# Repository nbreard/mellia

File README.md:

# MD10 board

Environnement setup : 

Software :

 STM32CubeIDE : for compilation debugging and flashing 
		
 STM32CubeProgrammer: for deactivate write protection bit

Hardware : LoRaWAN gateway connected to LoRaWAN server (TTN)

# MELLIA - Kit Dadant 10

## Présentation

Le kit Mellia Dadant 10 est un ensemble de capteurs connectés permettant d’obtenir des informations essentielles relatives à l’exploitation d’une ruche dans l’objectif de suivre l’évolution de la colonie en réduisant le nombre d’interventions intrusives et les déplacement de l’apiculteur.

Ce kit s’adapte sur une ruche Dadant 10, le modèle le plus utilisé actuellement. Il comprend un dispositif de pesée électronique, un dispositif de mesure de température et humidité intérieure et extérieure, un capteur de pression atmosphérique ainsi qu’un module de communication sans fil. L’ensemble des acquisitions sont enregistrées dans une base de données, un tableau de bord permet le suivi de l’état de la ruche.

## Fonctionnalités

### Mesure poids de la ruche

On pèse la ruche à intervalle régulier pour faire remonter une donnée sur la masse à l’apiculteur. Cela permet d’obtenir un indice de l’état de santé de la colonie et d’envisager d’intervenir ou non sur la ruche (rajout de candi, miellée etc). 

### Température extérieure

Une captation de température dans l’environnement immédiat de la ruche renseigne l’apiculteur sur la météo du milieu dans lequel évolue la colonie d’abeille et donne la capacité d’anticiper une miellée par exemple.

### Température intérieure

La mesure de la température à l’intérieur de la ruche fournis une information sur l’état de santé du couvain. Pour se développer correctement sa température doit rester dans une plage de mesure de 18 à 35°C. Sortir de cette plage indique un danger pour la colonie. Des variations régulières de la température est un signe d’essaimage.

### Humidité extérieure

Utile au rafraîchissement de la ruche ou intervenant directement dans la probabilité de voir se développer des champignons, le taux d’humidité intervient directement dans la vie de la colonie et le mesurer peut se révéler être un élément clé pour comprendre l’activité de la ruche.

### Humidité intérieure

Cette donnée a une incidence sur l’état de santé du couvain, en effet si celui ci est trop humide les parois en deviennent fragiles. Le taux d’humidité est aussi un bon indicateur de la qualité du miel.

### Pression atmosphérique

En corrélation avec l’humidité et la température extérieure, la pression atmosphérique fournit à l’apiculteur une vision globale sur le milieu à proximité de la ruche et sur les éléments auxquels sont soumis les abeilles 

### [Tableau de bord](https://grafana.mellia.lab.open.studio/login "https://grafana.mellia.lab.open.studio/login")

Pour faciliter l’information et la prise de décision les données sont rassemblées dans un tableau de bords consultable en ligne.

## Notice

### Composants du kit

Pour les composants sur la carte se référer au document md10-board/hardware/wheather_board_v1/wheather_board_v1.csv

| composant                            | référence                |
| ------                               | ------                   |
| jauge de contrainte                  | tedea 1242               |
| antenne                              | MOLEX  105262-0001       |
| boîtier                              | TAM 131007 ENCLOSURE     |
| panneau solaire + batterie           |                          |

### Montage

### Mise en œuvre

## Software 

**Prérequis** : 

Télécharger le logiciel STM32CubeIDE : <https://www.st.com/en/development-tools/stm32cubeide.html>

Télécharger le logiciel STM32CubeProgrammer : <https://www.st.com/en/development-tools/stm32cubeide.html>

Télécharger le code grâce à la commande suivante : 

Git clone <https://gitlab.openstudio-lab.com/mellia/mellia.git>

**Ouvrir le projet :** 

Ouvrir stm32CubeIde, sélectionner ~/md10-board/software/ruche\_soft comme workspace

Depuis STM32CubeIDE, cliquer sur File et « Open Project from file system »

Dans la fenêtre qui s’ouvre cliquer sur directory et sélectionner : ~/md10-board/software/ruche\_soft/STM32Cube\_FW\_WL\_V1.1.0/Projects/NUCLEO-WL55JC/Applications/LoRaWAN/LoRaWAN\_End\_Node/STM32CubeIDE

Les librairies des composants sont accessibles depuis Drivers. Le dossier Sensors contient les fonctions des différentes de mesures, poids, température etc.

Application contient le code de la machine à état qui fait tourner le programme mais aussi les drivers des périphériques de communication tel que le SPi l’i2c ou encore le protocole de communication LoRaWAN servant à faire remonter les données.

L’acquisition des mesures est faite au cours de la fonction SendTxData située dans lora\_app.c

**Flasher le programme :**

Connecter le debugger : 

Se connecter au microcontrolleur en utilise STM32Cubeprogramme et désactiver la protection en écriture : 

Pour lancer le debugger depuis stmcubeide appliquer cette configuration depuis Run -> debug configuration : 

Attention pour des raisons d’optimisation la sonde de debug et le mode low power est activé. Pour faire plus que flasher le code est debugger en mode pas à pas il faut se rendre dans sys\_conf.h et régler sur 1 les #define suivants : DEBUGGER\_ENABLED et LOW\_POWER\_DISABLE

**Procédure de calibration de la balance** 

On utilise les équations données par TI dans le document relatif à la bonne utilisation de la carte ADS1242 : 

On a besoin de 3 paramètres : 

- wfs  : la masse la plus proche possible de la pleine échelle
- Cfs  : la sortie de l’dc correspondant à wfs
- Czs : la sortie de l’adc lorsque la balance est à vide

À l’aide de ces trois données on peut en déduire l’équation 1 puis la 2 . On place un points d’arrêt dans le code après la mesure pour récupérer cfs et czs.

Les paramètres wzs et m sont à introduire en dur dans le code dans la fonction d’initialisation de l’ads1232 : void ADS1232Sensors\_Init(sensor\_t \*sensor\_data) 

Lors de l'assemblage d'une nouvelle balance, il est important de sélectionner les variables pour une jauge de 100kg ou de 250kg dans la fonction ADS1232Sensors_Init() contenu dans weight_sensor.c

#### Node-red

Node-red est un outil de développement basé sur les flux. Il sert ici à récupérer les données en provenance du broker MQTT fournit par TTN et à les enregistrer dans une base de donnée influxDB. Les ressources pour le déployer se situe dans le répertoir software

Pour se connecter au broker on commence par ajouter le module MQTT à l'interface node red en suivant ce tutoriel : 
https://www.thethingsnetwork.org/forum/t/mqtt-in-node-red-howto/39909

NB : nous utilisons Orange plutôt que TTN pour recevoir les données LoRa mais le principe est le même

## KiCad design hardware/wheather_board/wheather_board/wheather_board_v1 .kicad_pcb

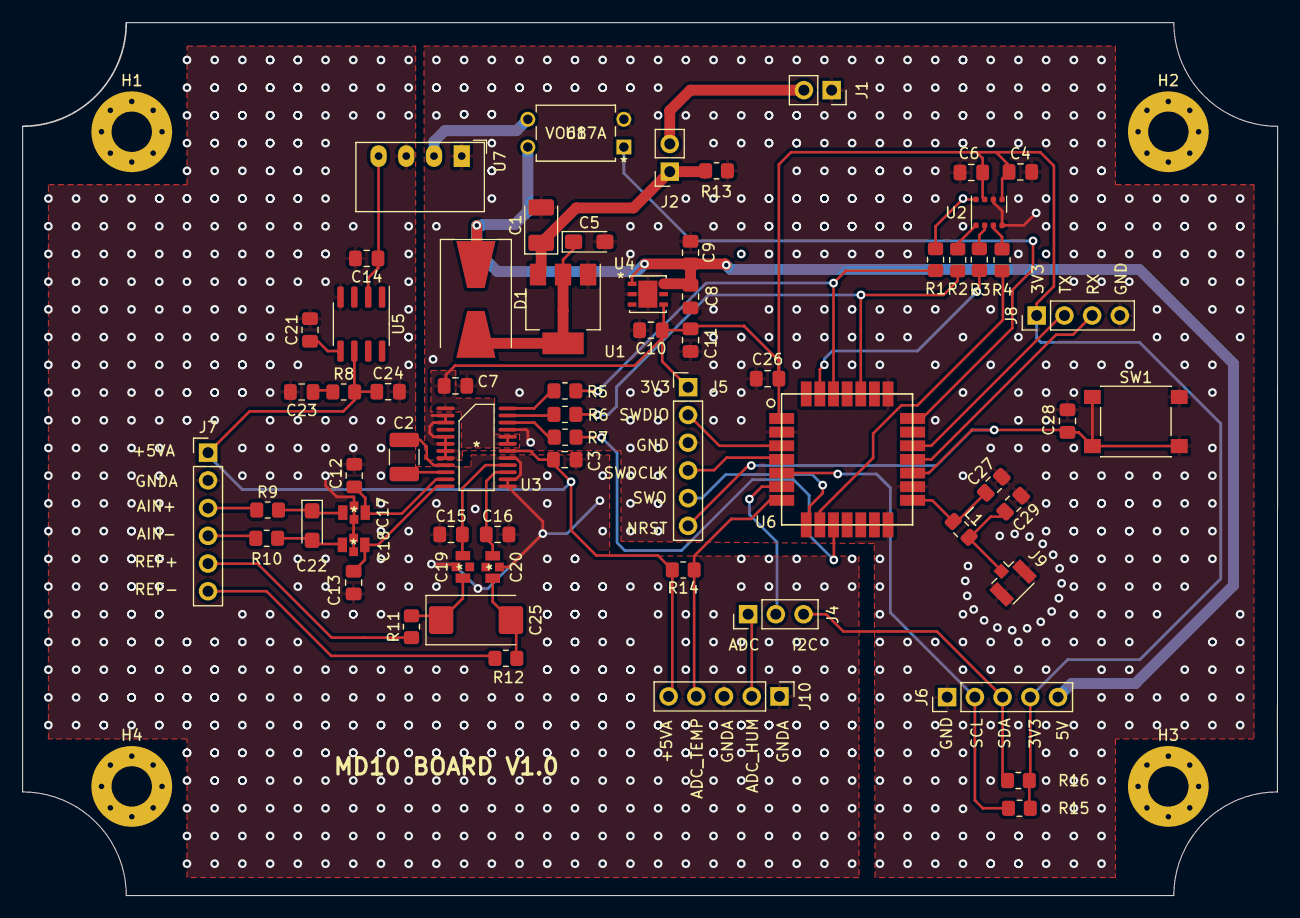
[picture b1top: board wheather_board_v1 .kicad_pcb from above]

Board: 2 copper layers, 115.0 x 80.0 mm, 69 parts (0 on the bottom side), 53 nets.

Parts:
C1: 10uF; CP_EIA-3528-21_Kemet-B_Pad1.50x2.35mm_HandSolder
C2: 0.1uF; C_1210_3225Metric_Pad1.33x2.70mm_HandSolder
C3, C7: 2.2uF; C_0805_2012Metric_Pad1.18x1.45mm_HandSolder
C4, C6, C9, C11, C28: 100nF; C_0805_2012Metric_Pad1.18x1.45mm_HandSolder
C5: 10uF; CP_EIA-3216-18_Kemet-A_Pad1.58x1.35mm_HandSolder
C8, C10, C21, C24: 1uF; C_0805_2012Metric_Pad1.18x1.45mm_HandSolder
C12, C13, C15, C16: 100pF; C_0805_2012Metric_Pad1.18x1.45mm_HandSolder
C14: 1uF to 10 uF; C_0805_2012Metric_Pad1.18x1.45mm_HandSolder
C17, C18, C19, C20: C_Feedthrough; NFM21PC105B1C3D
C22: 0.1uF; CP_EIA-3216-18_Kemet-A
C23: 1uF to 50uF; C_0805_2012Metric_Pad1.18x1.45mm_HandSolder
C25: 100uF; CP_EIA-7343-31_Kemet-D_Pad2.25x2.55mm_HandSolder
C26: 4.7uF; C_0805_2012Metric_Pad1.18x1.45mm_HandSolder
C27, C29: dnp; C_0805_2012Metric_Pad1.18x1.45mm_HandSolder
D1: D; D_SMB-SMC_Universal_Handsoldering
H1, H2, H3, H4: MountingHole; MountingHole_3.7mm_Pad_Via
J1: Conn_01x02_Female; PinSocket_1x02_P2.54mm_Vertical
J2: Conn_01x02_Male; PinSocket_1x02_P2.54mm_Vertical
J4: Conn_01x03_Male; PinHeader_1x03_P2.54mm_Vertical
J5: Conn_01x06_Male; PinHeader_1x06_P2.54mm_Vertical
J6, J10: Conn_01x05_Female; PinHeader_1x05_P2.54mm_Vertical
J7: Conn_01x06_Female; PinHeader_1x06_P2.54mm_Vertical
J8: Conn_01x04_Male; PinHeader_1x04_P2.54mm_Vertical
J9: Conn_Coaxial; U.FL_Hirose_U.FL-R-SMT-1_Vertical
L1: dnp; L_0805_2012Metric_Pad1.15x1.40mm_HandSolder
R1, R2, R3, R4, R15, R16: R; R_0805_2012Metric_Pad1.20x1.40mm_HandSolder
R5, R6, R7: 22; R_0805_2012Metric_Pad1.20x1.40mm_HandSolder
R8: 1; R_0805_2012Metric_Pad1.20x1.40mm_HandSolder
R9, R10, R13: 0; R_0805_2012Metric_Pad1.20x1.40mm_HandSolder
R11, R12: 100; R_0805_2012Metric_Pad1.20x1.40mm_HandSolder
R14: 10k; R_0805_2012Metric_Pad1.20x1.40mm_HandSolder
SW1: SW_MEC_5G; SW_SPST_PTS645
U1: LD1117S50TR_SOT223; SOT-223-3_TabPin2
U2: BME680; Bosch_LGA-8_3x3mm_P0.8mm_ClockwisePinNumbering
U3: ADS1232IPW
U4: LD39050PUR
U5: REF5050AD; SOIC-8_3.9x4.9mm_P1.27mm
U6: LoRa-E5
U7: CRE1S0505SC; Converter_DCDC_muRata_CRE1xxxxxxSC_THT
U8: VO617A

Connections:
+3.3V: J6.4, R15.2, R16.2
+3V3: C4.1, C6.1, C7.2, C10.1, C11.1, C26.1, J5.1, J8.1, U2.6 (VDDIO), U2.8 (VDD), U3.1 (DVDD), U3.19 (GAIN0), U3.20 (GAIN1), U4.4 (VOUT), U6.1 (VCC)
+5V: C8.2, C9.2, D1.1 (K), J6.5, U4.1 (EN), U4.6 (VIN), U8.4 (C)
+5VA: C3.1, C24.1, J7.1, J10.5, R8.2, R14.2, U3.18 (AVDD), U5.6 (Vout)
/ADC_HUM: J4.1, J10.2
/ADC_TEMP: J10.4, R14.1, U6.7 (PB4)
/ADS_NSS: R7.1, U6.10 (PB6)
/AIN+: J7.3, R9.1
/AIN-: J7.4, R10.1
/AINN1: C13.1, C18.3, U3.12 (AINN1)
/AINP1: C12.2, C17.1, U3.11 (AINP1)
/BME_NSS: R4.1, U6.9 (PB7)
/EN_VDDA: U6.21 (PA9), U8.1 (A)
/I2C_SCL: J6.2, R15.1, U6.5 (PB15)
/I2C_SDA: J4.3, J6.3, R16.1
/NRST: C28.2, J5.6, SW1.1 (A), SW1.2 (A), U6.17 (RST)
/REFN: C16.1, C20.3, U3.15 (REFN)
/REFP: C15.2, C19.1, U3.16 (REFP)
/SPI_MISO: R1.1, R5.1, U6.26 (PB14)
/SPI_MOSI: R3.1, U6.27 (PA10)
/SPI_SCK: R2.1, R6.1, U6.24 (PB13~)
/SWDCLK: J5.4, U6.4 (PA14)
/SWDIO: J5.2, U6.3 (PA13)
/SWO: J5.5, U6.8 (PB3)
/UART_RX: J8.3, U6.18 (PA3)
/UART_TX: J8.2, U6.19 (PA2)
/ref+: J7.5, R11.1
/ref-: J7.6, R12.1
/toref: C14.1, U5.2 (Vin), U7.4 (+VOUT)
GND: C1.2, C4.2, C5.2, C6.2, C7.1, C8.1, C9.1, C10.2, C11.2, C26.2, C27.2, C28.1, C29.2, J1.1, J5.3, J6.1, J8.4, J9.2 (Ext), R13.1, SW1.1 (A), SW1.2 (A), U1.1 (GND), U2.1 (GND), U2.7 (GND), U3.2 (DGND), U3.3 (CLKIN/XTAL1), U3.5 (DGND), U3.6 (DGND), U3.7 (TEMP), U3.8 (A0), U3.21 (SPEED), U4.2 (GND), U4.7 (GND), U6.2 (GND), U6.14 (GND), U6.16 (GND), U6.22 (GND), U7.1 (-VIN), U8.2 (C)
GNDA: C3.2, C12.1, C13.2, C14.2, C15.1, C16.2, C17.2, C18.2, C19.2, C20.2, C21.2, C23.2, C24.2, J7.2, J10.1, J10.3, U3.13 (AINN2), U3.14 (AINP2), U3.17 (AGND), U5.4 (GND), U7.3 (-VOUT)
unnamed: C1.1, J2.1, R13.2, U1.3 (VI)
unnamed: C2.1, U3.9 (CAP)
unnamed: C2.2, U3.10 (CAP)
unnamed: C5.1, D1.2 (A), U1.2 (VO)
unnamed: C17.3, C22.1, R9.2
unnamed: C18.1, C22.2, R10.2
unnamed: C19.3, C25.1, R11.2
unnamed: C20.1, C25.2, R12.2
unnamed: C21.1, U5.5 (Trim/NR)
unnamed: C23.1, R8.1
unnamed: C27.1, L1.1, U6.15 (RFIO)
unnamed: C29.1, J9.1 (In), L1.2
unnamed: J4.2, U6.6 (PA15)
unnamed: R1.2, U2.5 (SDO)
unnamed: R2.2, U2.4 (SCK)
unnamed: R3.2, U2.3 (SDI)
unnamed: R4.2, U2.2 (CSB)
unnamed: R5.2, U3.24 (~DRDY/DOUT)
unnamed: R6.2, U3.23 (SCLK)
unnamed: R7.2, U3.22 (~PWDN)
unnamed: U7.2 (+VIN), U8.3 (E)
VCC: J1.2, J2.2

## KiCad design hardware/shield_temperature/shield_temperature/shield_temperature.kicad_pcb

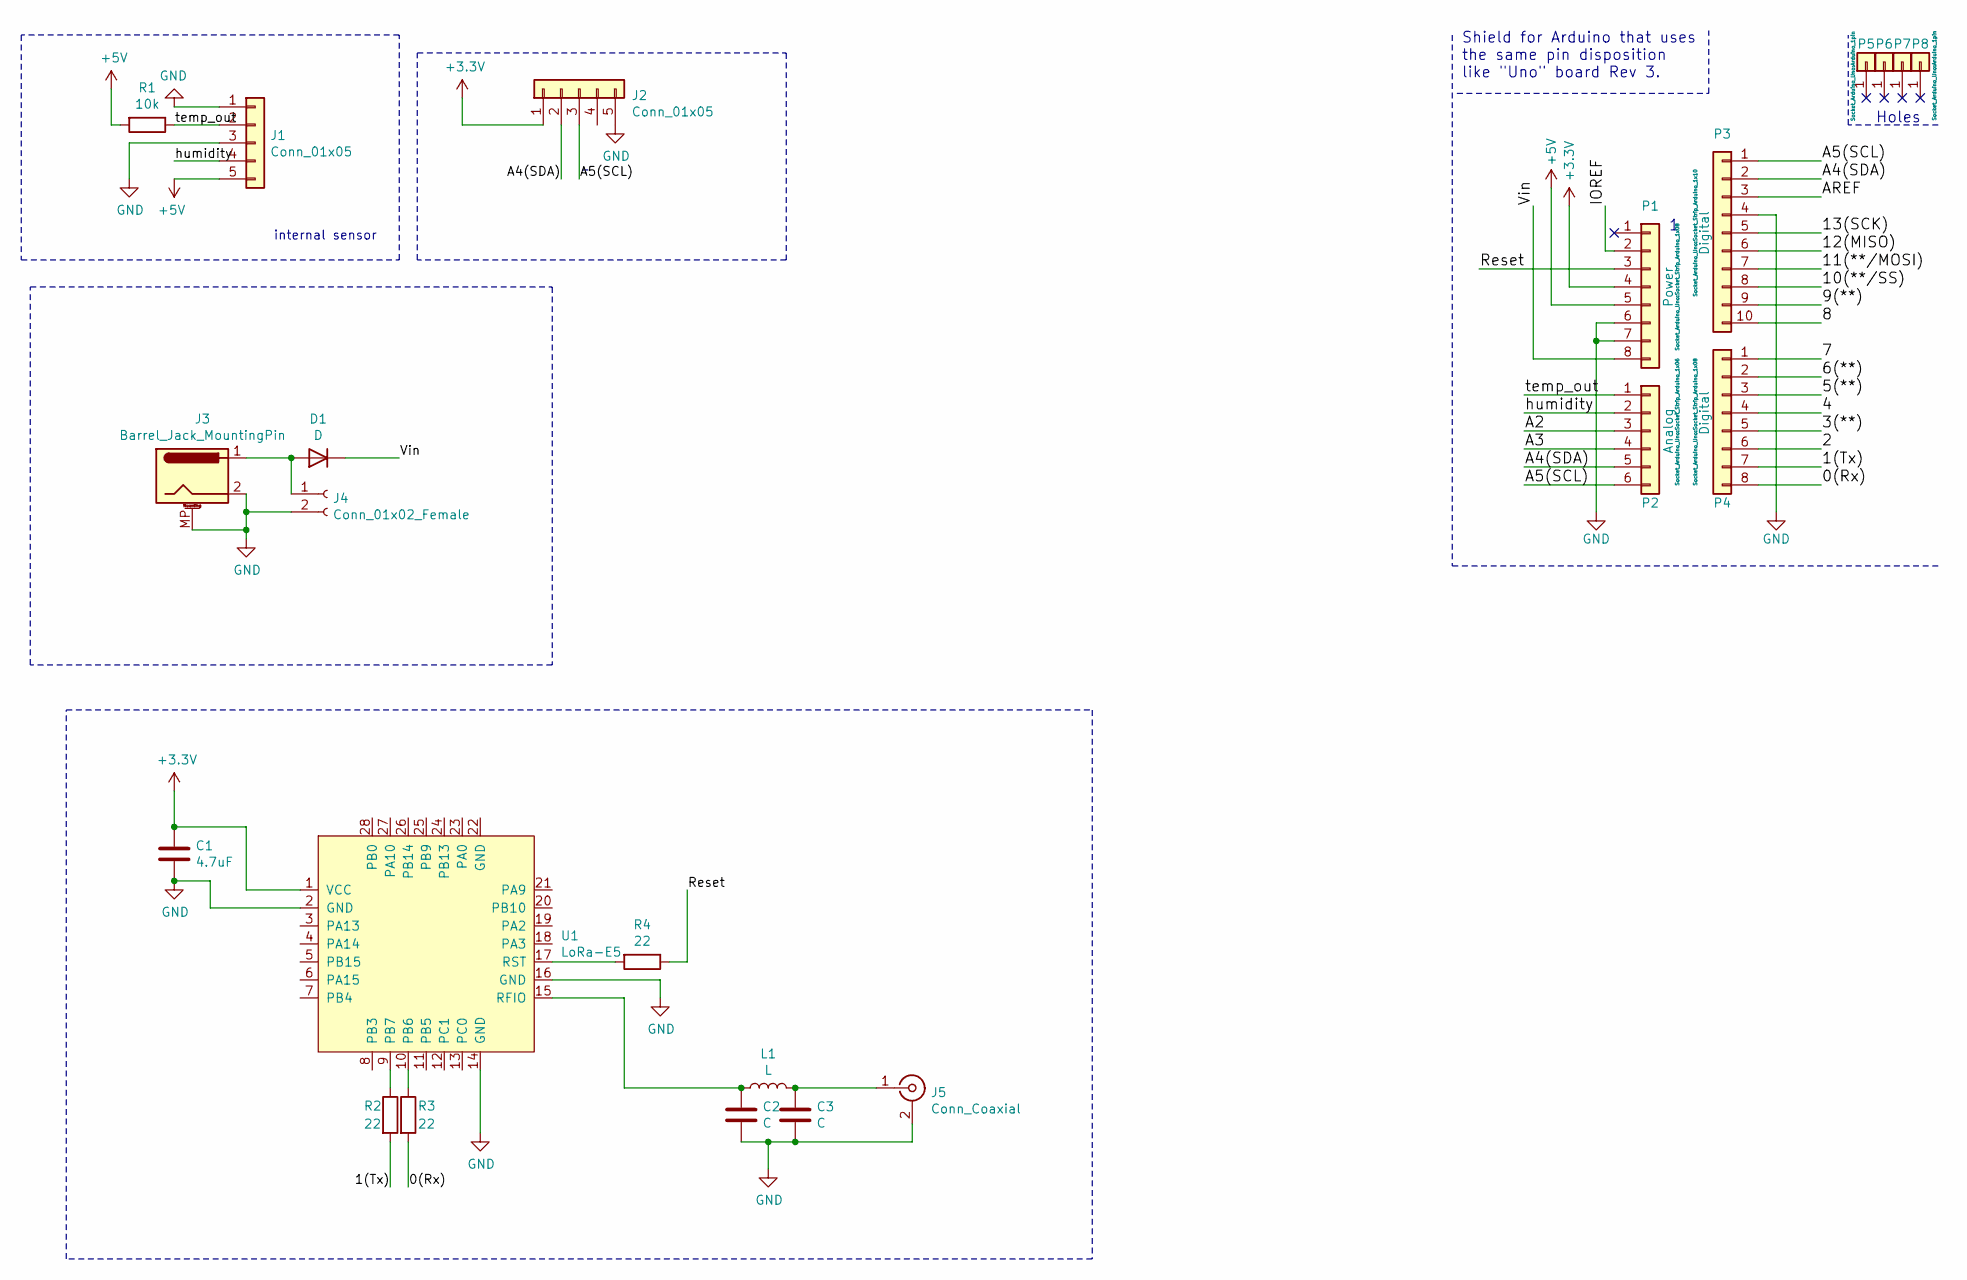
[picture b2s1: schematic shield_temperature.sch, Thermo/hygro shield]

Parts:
C1: 4.7uF; C_0805_2012Metric
C2, C3: C; C_0805_2012Metric
D1: D; D_SMB
J1: Conn_01x05; D_SMB
J2: Conn_01x05; PinHeader_1x05_P2.54mm_Vertical
J3: Barrel_Jack_MountingPin; BarrelJack_Horizontal
J4: Conn_01x02_Female; PinHeader_1x02_P2.54mm_Vertical
J5: Conn_Coaxial; U.FL_Hirose_U.FL-R-SMT-1_Vertical
L1: L; L_0805_2012Metric_Pad1.05x1.20mm_HandSolder
P1: Power; Socket_Strip_Arduino_1x08
P2: Analog; Socket_Strip_Arduino_1x06
P3: Digital; Socket_Strip_Arduino_1x10
P4: Digital; Socket_Strip_Arduino_1x08
P5, P6, P7, P8: CONN_01X01; Arduino_1pin
R1: 10k; R_1206_3216Metric
R2, R3, R4: 22; R_0805_2012Metric
U1: LoRa-E5

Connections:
+3V3: C1.1, J2.1, P1.4, U1.1 (VCC)
+5V: J1.5, P1.5, R1.2
/0(Rx): P4.8, R3.2
/1(Tx): P4.7, R2.2
/2: P4.6
/3(**): P4.5
/4: P4.4
/5(**): P4.3
/6(**): P4.2
/7: P4.1
/8: P3.10
/9(**): P3.9
/10(**/SS): P3.8
/11(**/MOSI): P3.7
/12(MISO): P3.6
/13(SCK): P3.5
/A2: P2.3
/A3: P2.4
/A4(SDA): J2.2, P2.5, P3.2
/A5(SCL): J2.3, P2.6, P3.1
/AREF: P3.3
/IOREF: P1.2
/Reset: P1.3, R4.1
/Vin: D1.1 (K), P1.8
/humidity: J1.4, P2.2
/temp_out: J1.2, P2.1, R1.1
GND: C1.2, C2.2, C3.2, J1.1, J1.3, J2.5, J3.2, J3.MP (MountPin), J4.2, J5.2 (Ext), P1.6, P1.7, P3.4, U1.2 (GND), U1.14 (GND), U1.16 (GND)
unnamed: C2.1, L1.1, U1.15 (RFIO)
unnamed: C3.1, J5.1 (In), L1.2
unnamed: D1.2 (A), J3.1, J4.1
unnamed: R2.1, U1.9 (PB7)
unnamed: R3.1, U1.10 (PB6)
unnamed: R4.2, U1.17 (RST)

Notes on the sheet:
Holes
Shield for Arduino that uses the same pin disposition like "Uno" board Rev 3.
internal sensor

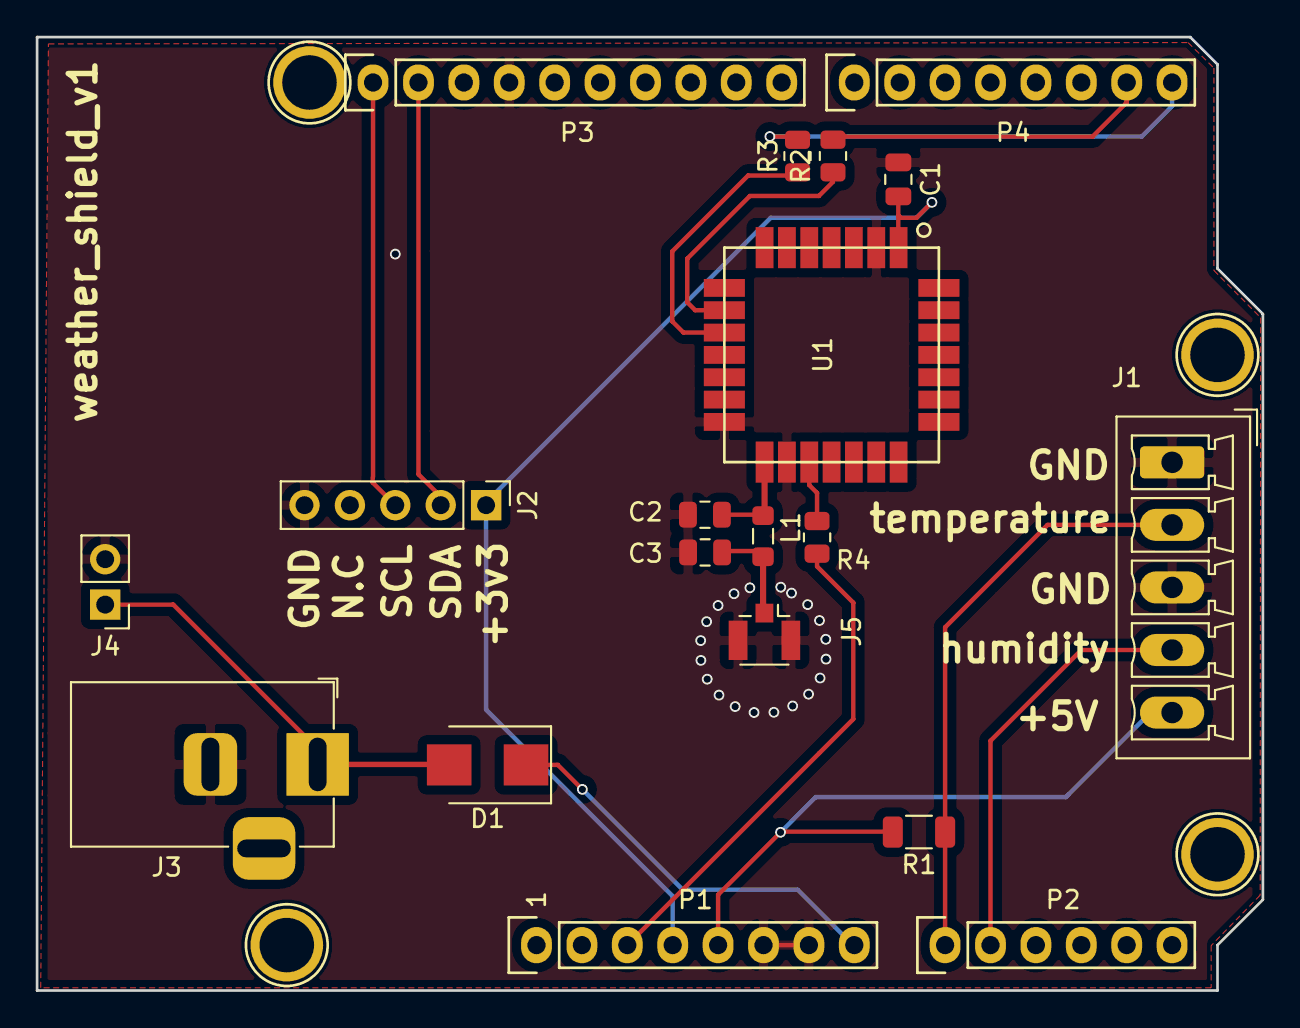
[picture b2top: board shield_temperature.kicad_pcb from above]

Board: 2 copper layers, 68.6 x 53.3 mm, 23 parts (0 on the bottom side), 17 nets.

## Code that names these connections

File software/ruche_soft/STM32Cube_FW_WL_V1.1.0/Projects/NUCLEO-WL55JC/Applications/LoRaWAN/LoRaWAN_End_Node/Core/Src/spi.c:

/* USER CODE BEGIN Header */
/**
  ******************************************************************************
  * @file         spi.c
  * @brief        This file provides code for the MSP Initialization
  *               and de-Initialization codes.
  ******************************************************************************

/* Includes ------------------------------------------------------------------*/
#include "spi.h"
/* USER CODE BEGIN Includes */

/* USER CODE END Includes */
SPI_HandleTypeDef hspi2;

void MX_SPI2_Init(void)
{

  /* USER CODE BEGIN SPI2_Init 0 */

  /* USER CODE END SPI2_Init 0 */

  /* USER CODE BEGIN SPI2_Init 1 */

  /* USER CODE END SPI2_Init 1 */
  /* SPI2 parameter configuration*/
  hspi2.Instance = SPI2;
  hspi2.Init.Mode = SPI_MODE_MASTER;
  hspi2.Init.Direction = SPI_DIRECTION_2LINES;
  hspi2.Init.DataSize = SPI_DATASIZE_8BIT;
  hspi2.Init.CLKPolarity = SPI_POLARITY_HIGH;
  hspi2.Init.CLKPhase = SPI_PHASE_2EDGE;
  hspi2.Init.NSS = SPI_NSS_SOFT;
  hspi2.Init.BaudRatePrescaler = SPI_BAUDRATEPRESCALER_2;
  hspi2.Init.FirstBit = SPI_FIRSTBIT_MSB;
  hspi2.Init.TIMode = SPI_TIMODE_DISABLE;
  hspi2.Init.CRCCalculation = SPI_CRCCALCULATION_DISABLE;
  hspi2.Init.CRCPolynomial = 7;
  hspi2.Init.CRCLength = SPI_CRC_LENGTH_DATASIZE;
  hspi2.Init.NSSPMode = SPI_NSS_PULSE_DISABLE;
  if (HAL_SPI_Init(&hspi2) != HAL_OK)
  {
    Error_Handler();
  }
  /* USER CODE BEGIN SPI2_Init 2 */

  /* USER CODE END SPI2_Init 2 */

}

/**
* @brief SPI MSP Initialization
* This function configures the hardware resources used in this example
* @param hspi: SPI handle pointer
* @retval None
*/
void HAL_SPI_MspInit(SPI_HandleTypeDef* hspi)
{
  GPIO_InitTypeDef GPIO_InitStruct = {0};
  RCC_PeriphCLKInitTypeDef PeriphClkInitStruct = {0};
  if(hspi->Instance==SPI2)
  {
  /* USER CODE BEGIN SPI2_MspInit 0 */

  /* USER CODE END SPI2_MspInit 0 */

  /** Initializes the peripherals clocks
  */
    PeriphClkInitStruct.PeriphClockSelection = RCC_PERIPHCLK_I2S2;
    PeriphClkInitStruct.I2s2ClockSelection = RCC_I2S2CLKSOURCE_HSI;
    if (HAL_RCCEx_PeriphCLKConfig(&PeriphClkInitStruct) != HAL_OK)
    {
      Error_Handler();
    }

    /* Peripheral clock enable */
    __HAL_RCC_SPI2_CLK_ENABLE();

    __HAL_RCC_GPIOB_CLK_ENABLE();
    __HAL_RCC_GPIOA_CLK_ENABLE();
    /**SPI2 GPIO Configuration
    PB14     ------> SPI2_MISO
    PA10     ------> SPI2_MOSI
    PB13     ------> SPI2_SCK
    */
    GPIO_InitStruct.Pin = GPIO_PIN_14|GPIO_PIN_13;
    GPIO_InitStruct.Mode = GPIO_MODE_AF_PP;
    GPIO_InitStruct.Pull = GPIO_NOPULL;
    GPIO_InitStruct.Speed = GPIO_SPEED_FREQ_LOW;
    GPIO_InitStruct.Alternate = GPIO_AF5_SPI2;
    HAL_GPIO_Init(GPIOB, &GPIO_InitStruct);

    GPIO_InitStruct.Pin = GPIO_PIN_10;
    GPIO_InitStruct.Mode = GPIO_MODE_AF_PP;
    GPIO_InitStruct.Pull = GPIO_NOPULL;
    GPIO_InitStruct.Speed = GPIO_SPEED_FREQ_LOW;
    GPIO_InitStruct.Alternate = GPIO_AF5_SPI2;
    HAL_GPIO_Init(GPIOA, &GPIO_InitStruct);

  /* USER CODE BEGIN SPI2_MspInit 1 */
    /*Configure GPIO pin Output Level */

    /*Configure GPIO pins : BME_NSS_Pin ADS_NSS_Pin */
    GPIO_InitStruct.Pin = BME_NSS_Pin|ADS_NSS_Pin;
    GPIO_InitStruct.Mode = GPIO_MODE_OUTPUT_PP;
    GPIO_InitStruct.Pull = GPIO_NOPULL;
    GPIO_InitStruct.Speed = GPIO_SPEED_FREQ_LOW;
    HAL_GPIO_Init(GPIOB, &GPIO_InitStruct);

    HAL_GPIO_WritePin(GPIOB, BME_NSS_Pin|ADS_NSS_Pin, GPIO_PIN_SET);

  /* USER CODE END SPI2_MspInit 1 */
  }

}

/**
* @brief SPI MSP De-Initialization
* This function freeze the hardware resources used in this example
* @param hspi: SPI handle pointer
* @retval None
*/
void HAL_SPI_MspDeInit(SPI_HandleTypeDef* hspi)
{
  if(hspi->Instance==SPI2)
  {
  /* USER CODE BEGIN SPI2_MspDeInit 0 */

  /* USER CODE END SPI2_MspDeInit 0 */
    /* Peripheral clock disable */
    __HAL_RCC_SPI2_CLK_DISABLE();

    /**SPI2 GPIO Configuration
    PB14     ------> SPI2_MISO
    PA10     ------> SPI2_MOSI
    PB13     ------> SPI2_SCK
    */
    HAL_GPIO_DeInit(GPIOB, GPIO_PIN_14|GPIO_PIN_13);

    HAL_GPIO_DeInit(GPIOA, GPIO_PIN_10);

  /* USER CODE BEGIN SPI2_MspDeInit 1 */

  /* USER CODE END SPI2_MspDeInit 1 */
  }

}

/* USER CODE BEGIN 1 */

/* USER CODE END 1 */

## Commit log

2022-12-19 add node-red ressources
2022-12-19 fix some hardware bugs and add an optocoupler

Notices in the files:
parts and their libraries:
Copyright 2021 Accelerated Designs. All rights reserved.
